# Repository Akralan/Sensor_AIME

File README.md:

# Solution IoT pour un capteur de gaz connecté

## 1. Introduction
**Contexte et Motivation :**  
Ce projet propose une solution IoT complète autour d’un capteur de gaz, intégrant la conception électronique (PCB, amplification, filtrage), le développement logiciel (firmware embarqué sur ESP32, interface Node-RED) et une application mobile (AppInventor).

**Description Générale :**  
Le système permet de mesurer la concentration de gaz via un capteur dédié, de conditionner le signal et de transmettre les données via LoRa ou Bluetooth. L’utilisateur peut ensuite visualiser les mesures en temps réel et interagir avec le dispositif depuis une interface Node-RED ou une application mobile.

---

## 2. Table des Matières
- [1. Introduction](#1-introduction)
- [2. Table des Matières](#2-table-des-matières)
- [3. Aperçu du Projet](#3-apercu-du-projet)
- [4. Matériel (Hardware)](#4-matériel-hardware)
- [5. Logiciel (Software)](#5-logiciel-software)
- [6. Installation et Mise en Service](#6-installation-et-mise-en-service)
- [7. Utilisation](#7-utilisation)
- [8. Contacts et Auteurs](#8-contacts-et-auteurs)

---

## 3. Aperçu du Projet

**Résumé Fonctionnel :**  
1. Mesure de gaz via un capteur spécifique et circuits d’acquisition (amplification, filtrage).  
2. Traitement et envoi des données par un microcontrôleur (ESP32).  
3. Visualisation en temps réel sur Node-RED et application mobile (AppInventor).

**Architecture Globale :**  
- **Capteur de Gaz** : Convertit la concentration de gaz en signal électrique.
- **Chaîne d’Acquisition** : Simulations LTSpice et conception PCB (fichiers dans `Chaine acquisition` et `PCB`).  
- **Microcontrôleur (ESP32)** : Gère la communication (LoRa/BLE) et le traitement des mesures avant l'enregistrement dans la base de données (code dans `Code/AIME`).  
- **Interface Node-RED** : Flows pour l’affichage des donneés dans une interface web simpliste (dossier `NodeRed`).  
- **Application Mobile** : Réalisée sous AppInventor (dossier `AppInventor` à la racine).

---

## 4. Matériel (Hardware)

**Liste des Composants :**
- **Capteur de gaz** (spécifique au projet ou type MQ)  
- **ESP32** (ou carte équivalente)  
- **Modules de communication** (LoRa, Bluetooth, etc.)  
- **Composants d’amplification et filtrage** (ex. LTC1050, résistances, condensateurs)  
- **PCB** (dossier `PCB`)  
  - Fichiers KiCad (ex. `GazSensor.kicad_pro`)  
  - Dossier `pcb_aime` pour les fichiers de fabrication

**Design et Schémas :**  
- Fichiers KiCad dans le dossier `PCB`.  
- Simulations LTSpice dans `Chaine acquisition`.

**Procédure d’Assemblage :**  
- Ouvrir le projet KiCad pour consulter le routage et générer les fichiers Gerber.  
- Souder les composants en suivant le BOM (Bill Of Materials) et le placement défini par le PCB.

---

## 5. Logiciel (Software)

**Composants Logiciels :**
- **Firmware Embarqué** : Dossier `Code/AIME` (PlatformIO)  
- **Interface Node-RED** : Fichier `flows.json` dans le dossier `NodeRed`  
- **Application Mobile** : Dossier `AppInventor` (fichiers sources AppInventor)

**Organisation du Code :**
- `Code/AIME/`
  - **platformio.ini** : Fichier de configuration PlatformIO  
  - **src/** : Code source principal (ex. `main.cpp`, `gaz_sensor.cpp`)  
  - **include/** : Fichiers d’en-tête (ex. `gaz_sensor.h`)  
  - **lib/** : Bibliothèques locales (si nécessaires)  
  - **test/** : Éventuels tests unitaires  
  - **.vscode/** : Paramètres spécifiques VS Code pour PlatformIO

---

## 6. Installation et Mise en Service

### Prérequis
- **Visual Studio Code (VS Code)**
- **PlatformIO IDE** : Extension à installer dans VS Code
- **C/C++ Extension** (recommandée)
- **Bibliothèques** : Spécifiées dans la section `[lib_deps]` du fichier `platformio.ini`

### Guide Pas-à-Pas
1. **Cloner le Dépôt**  
    (Depuis un terminal)
    
    ```
    git clone https://github.com/<user>/Sensor_AIME.git
    ```

2. **Ouvrir le Projet avec VS Code**  
    - Lancer VS Code  
    - Sélectionner *Open Folder* et choisir `Sensor_AIME/Code/AIME`

3. **Installer PlatformIO**  
    - Dans VS Code, aller dans l’onglet *Extensions*  
    - Rechercher “PlatformIO IDE” et cliquer sur *Install*

4. **Compiler le Firmware**  
    - Ouvrir la palette de commandes (Ctrl+Shift+P)  
    - Taper `PlatformIO: Build`  
    - Vérifier que la compilation se déroule sans erreur

5. **Téléverser le Firmware**  
    - Connecter la carte ESP32 au PC via USB  
    - Dans la palette de commandes, sélectionner `PlatformIO: Upload`  
    - Vérifier que le port série est correctement configuré dans `platformio.ini`

6. **Configurer Node-RED**  
    - Installer Node-RED si besoin (ex. `npm install -g node-red`)  
    - Lancer Node-RED via la commande `node-red`  
    - Importer le flow depuis `NodeRed/flows.json`

7. **Installer l’Application Mobile (AppInventor)**  
    - Le dossier `AppInventor` se trouve à la racine du dépôt  
    - Ouvrir le projet AppInventor sur [ai2.appinventor.mit.edu](https://ai2.appinventor.mit.edu/)  
    - Compiler le projet et installer l’APK sur un smartphone Android

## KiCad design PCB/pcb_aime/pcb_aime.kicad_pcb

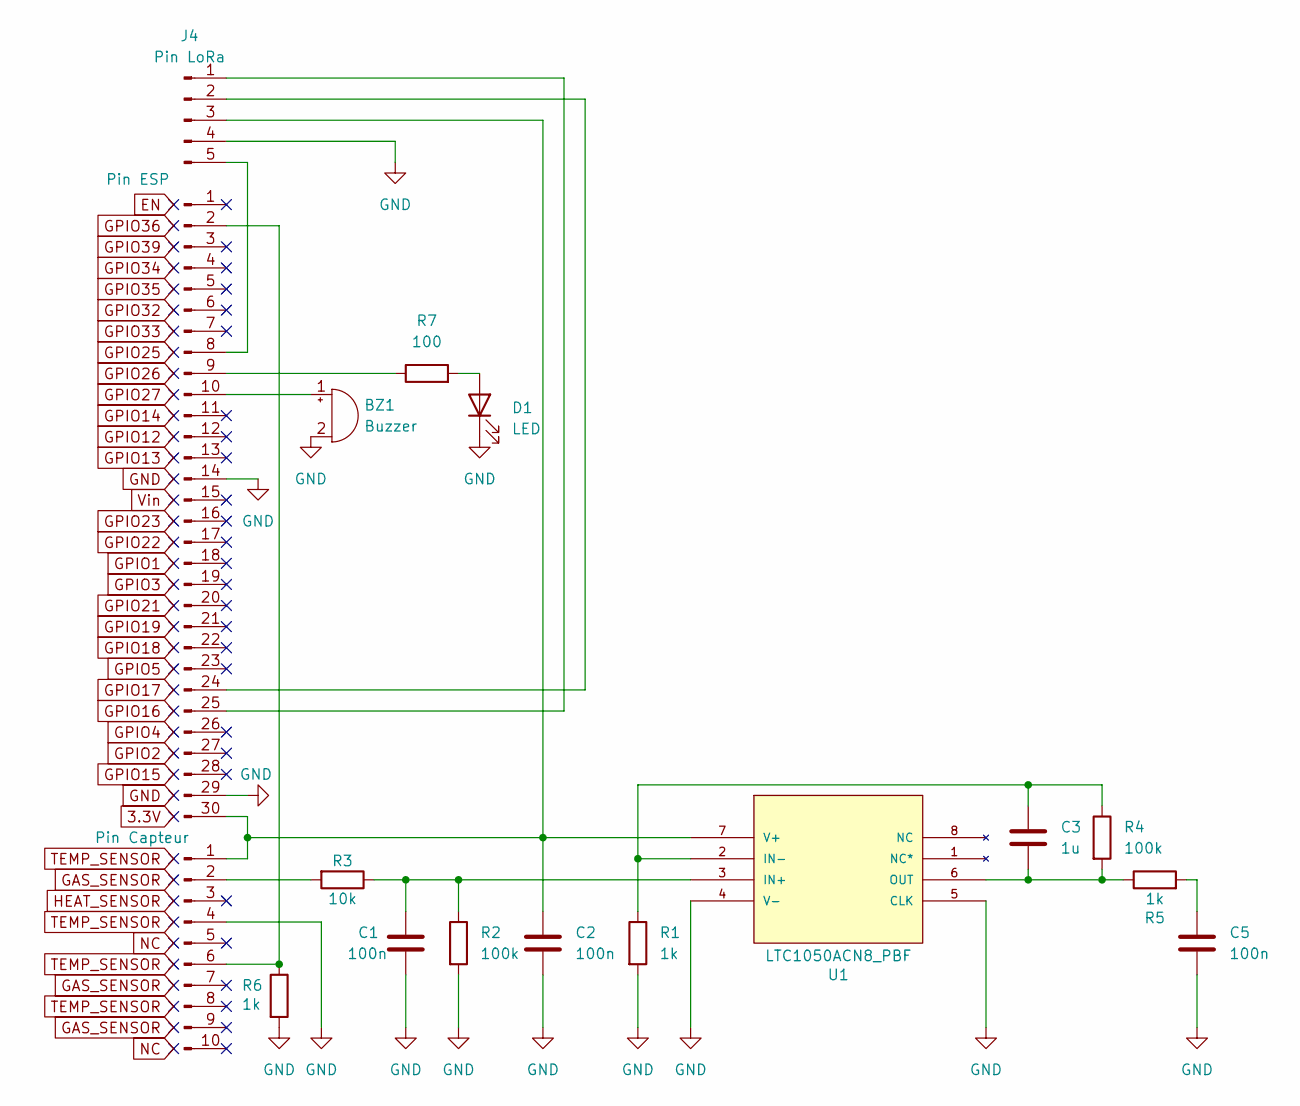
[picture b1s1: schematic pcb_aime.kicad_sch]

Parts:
BZ1: Buzzer; Buzzer_12x9.5RM7.6
C1, C2, C5: 100n; C_0805_2012Metric
C3: 1u; C_0805_2012Metric
D1: LED; LED_0805_2012Metric
J1: Pin ESP; XCVR_ESP32-C3-DEVKITM-1
J2: Pin Capteur; GazSensor
J4: Pin LoRa; PinHeader_1x05_P2.54mm_Vertical
R1, R5, R6: 1k; R_0805_2012Metric
R2, R4: 100k; R_0805_2012Metric
R3: 10k; R_0805_2012Metric
R7: 100; R_0805_2012Metric
U1: LTC1050ACN8_PBF; PDIP-8_N; MANUFACTURER_PART_NUMBER ltc1050acn8

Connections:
GND: BZ1.2 (-), C1.1, C2.1, C5.1, D1.1 (K), J1.14, J1.29, J2.4, J4.4, R1.2, R2.2, R6.2, U1.4 (V-), U1.5 (CLK)
unnamed: BZ1.1 (+), J1.10
unnamed: C5.2, R5.2
unnamed: D1.2 (A), R7.2
unnamed: J1.2, J2.6, R6.1
unnamed: J1.8, J4.5
unnamed: J1.9, R7.1
unnamed: J1.24, J4.2
unnamed: J1.25, J4.1
unnamed: C2.2, J1.30, J2.1, J4.3, U1.7 (V+)
unnamed: J2.2, R3.2
unnamed: C1.2, R2.1, R3.1, U1.3 (IN+)
unnamed: C3.2, R1.1, R4.1, U1.2 (IN-)
unnamed: C3.1, R4.2, R5.1, U1.6 (OUT)

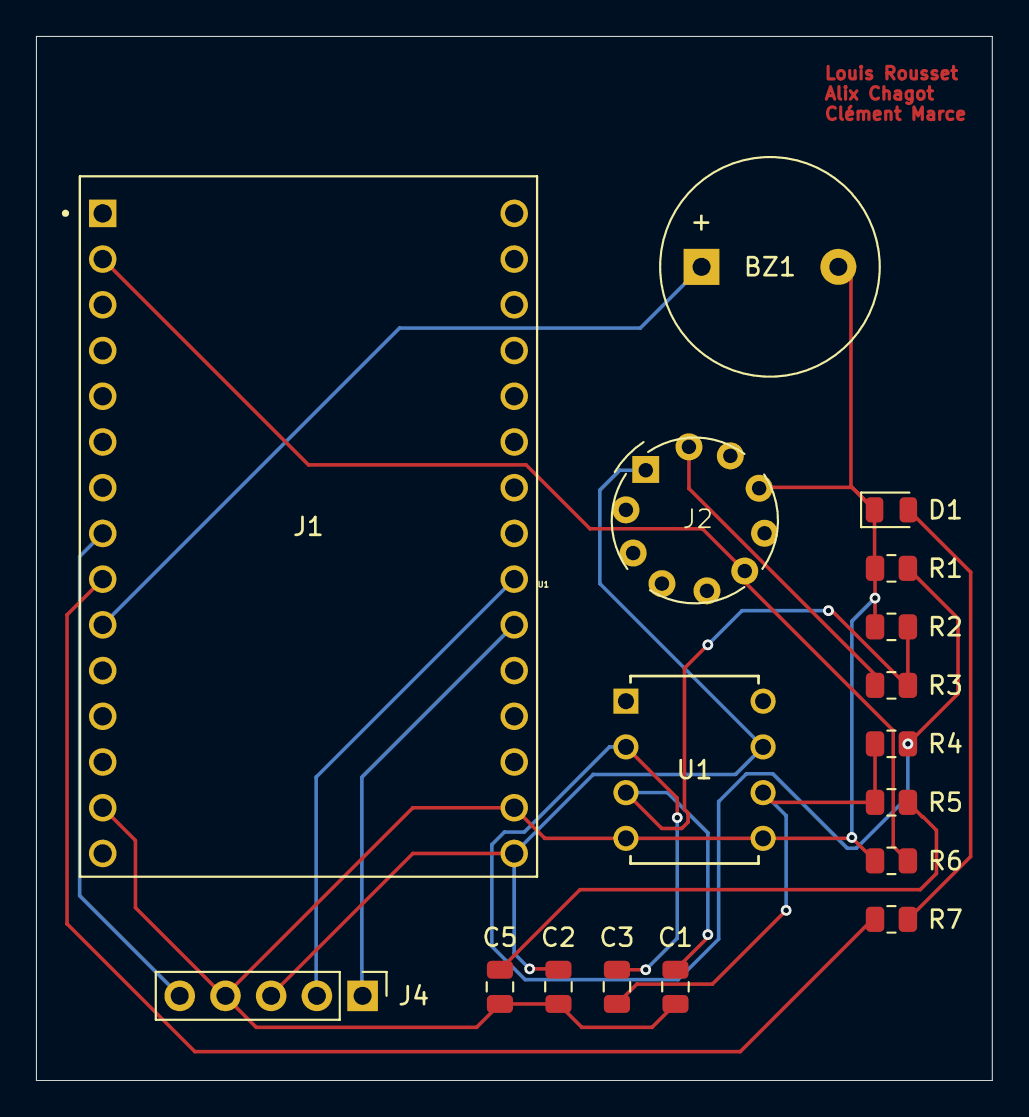
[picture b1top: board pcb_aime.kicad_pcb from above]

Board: 2 copper layers, 53.1 x 58.0 mm, 17 parts (0 on the bottom side), 14 nets.

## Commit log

2024-12-17 Ajout du code de l'esp32 pour se connecter à une application en bluetooth ainsi qu'à une base de donnée via un module LoRa afin de stocker les valeurs du capteur de gaz. Ajout du schéma électrique de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
2024-12-18 Modifications du code, ajout de la schématique et de la PCB définit pour avoir : Buzzer, led, capteur gaz et sa chaine d'acquisition, pin pour le module LoRa
2024-12-18 Ajout du nodered qui affiche sur le dashboard un chart des valeurs de gaz, la dernière valeur connus et une notification en cas de dépassement d'une valeur limite
2025-01-21 finishing some things
2025-02-25 ajout du code de l'application

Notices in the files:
parts and their libraries:
COPYRIGHT: Copyright C 2016 Accelerated Designs. All rights reserved
